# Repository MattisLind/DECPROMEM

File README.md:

# DECPROMEM

Project finished (almost) and deemed working as intended.

My 1 meg machine now shows 1536 kWord, i.e. 3 Mega byte of memory. The Gerbers in the kicad directory is updated. The final JED file to program the AYTF1508 is in the VHDL directory. Programming the board requires the rather expensive ATDH1150USB JTAG device. But supposedely other devices can be used. Check more here on [this page](https://github.com/peterzieba/5Vpld)

The board can be populated with either 1 or 2 chips. One chip will take your machine from 1 meg to the maximum of three meg. If you have less than 1 meg in your base machine a two chip card is better. The SIZE jumper need to be inserted if you only have one chip. 

The board can be populated with either AMD DP8307 bus tranceivers (which are obsolete but can be found online) or 74ALS640 which should be compatible. However not 100 % pincompatible, thus the overlapping layout.

I have not tested the board with one single chip or using 74ALS640 tranceivers (but it has been tested in simulation).

Debugging of the card took some time. Problems found during debugging:

1. The height of the card was 100 mil to high. Had to carefully cut off the card a bit to get it into the card cage. Lessons learned: Always double (triple) check dimensions. The new layout has this fixed.
2. The brand new 20 MHz crystal from Mouser didn't oscillate. While investigating this I found that certain signals of the Microchip 25LC08A SPI EEPROM require a 50 ns setup time. With a 20 MHz that would be on the margin unless the state machine was modified. I used a 14.7456 MHz crystal oscillator that I happened to find in my drawer.
3. SDENL need to be gated with with signals that indicate that the card is selected. Either IO read or memory read. Otherwise it will clash with other drivers on the bus.
4. The schematic had mixed up the MCELOW, NMCEHIGH and MLE signals. The good thibng it was easy to reroute those signals in the CPLD.
5. The BRPLYL signal was not developed internally. The OC signal was created by setting the signal to either 0 or Z. Somehow Yosys optimzed this away unless I set an attribute on those signal.
6. The BIOSEL signal has to be latched as an address signal. But since the SSxL signal is basically created with the latched BIOSEL on the motherboard there is no point in using BIOSEL anyway. Removed it from the CPLD VHLD logic.
7. The test bench for the SPI ROM wasn't perfect. It mismatched a bit from how reality worked so the SPI communication didn't work properly. The counter has to be incremented on falling edge instead of rising edge. Lessons learned is that good testbed is crucial. Still need to fix that SPIROM test device which still do the wrong thing.
8. When testing it read random number of bytes from the SPI ROM. Sometimes 30 sometimes 50. A metastability issues caused the HOLDL signal to get stuck. Syncing the readPort0 signal on the rising edge solved the problem.
9. The memoryAccess signal generated was spuriously active. Lilkely to be an effect of the fact that it is developed by a long chain of logic which ripples through. By syncing the memoryAccess signal with the clock and gating the clock to with the ASL signal solved the problem. Also making sure that all variables used in the process is the same length.

The development board with a lot of test points.

The original board:

This project aims at creating a modern memory board for the 1985 vintage DEC Professional series of computers with CTI bus. The idea is to use SRAM technology and programmable logic to implement all the random logic needed. The diagnostic ROM that all CTI bus boards need to have is implemented in a SPI EEPROM chip. The programmable logic choosen for this project is the Atmel / Microchip ATF1508 since it is the only contemporary chip that is 5V. I will be using one or two 1Mx16 SRAM chip which also are 5V. A small SPI EEPROM will contain the diag software. There will not be any parity on board whihc means that the diag software need to be changed compared to the original so that it doesn't test the parity generating and checking circuits on board.

The idea with this project is also to learn a bit about the CTI bus so that I can take on the DECNA-replica project later on which aims at creating a modern replacement for the DECNA board whihc is nearly impossible to find. This will also be using a ATF1508 CPLD.

## Firmware

The original diagnostic firmware is stored in either a 2716 or 2732 (jumper selectable on the board according to the manual), but only the lower 1k byte is actually used. 

I have been using xhomer project which I modified to create an execution trace. Thereby I could figure out how the Professional is dealing with CTI bus boards.
All boards has a board ID which identify the board. This is a two byte octal number which is also printed on the board handle. The memory board is 34 for example. Most likely the board id has significance to how the board is handled but I have obnly researched the memory board this far.

All CTI bus boards have a writeable register located at base address + 2 which resets the pointer to the ID / diagnostic ROM when written to it. Then reads from the base address will return byte by byte from the ID / diag ROM. The process is the following:

1. Read the two ID bytes. Decide how to handle board.
2. Reset pointer and read the first 12 bytes into memory. Byte 2 is compared with 0377. I am not sure what happens if it is not matching. Then it uses byte 6 to indicate the number of 128 word blocks that are present in the memory.
3. It resets the pointer again and start reading the number indicated byte location 6 above of 128 word blocks and calculates a checksum. More on the checksum algorithm later.
4. It then resets the pointer again and just read and skip the first 12 bytes. Then it reads in the following 14 bytes.
5. Location 23 and 24 is the size of the actual program code following, where byte 23 is the low byte and 24 is the high byte. The resuling 16 bit integer is then used when reading in the program code.
6. While reading the program code the same type of checksum is calculated again over this smaller block.

### Checksum algorithm

The checksum algorithm is a combination of xor and shift operations.
1. A checksum accumulator is initiated to 0177777
2. Two bytes are read in to form a word.
3. The data is xor:ed with the accumulator contents.
4. The accumulator is shifted on step to the left.
5. The bit overflowing 16 bits is creating a carry bit which either one or zero.
6. The carry bit is added to the accumulator.
7. The process repeats at 2 until all words has been read.
8. If the result in the accumulator is zero when all words has vbeen read then we have a good checksum.

### Firmware functions

The firmware is used to initialize and test the board. The process is the following:
1. Calculates the size of the board. There are two jumpers on the board which give the actual size of the board. I think actually this calculation is buggy for boards with 256 k chips!
2. It compares the calculated size with the value used as base value for this memory array. If the base address indicate that we already configured 3 Megabytes of memory we bail out with an error code.
3. Enable the memory board with the base value given from the system.
4. If memory size of the board give that it will exceed the 3 meg limit it tests so that there is no response from the memory for addresses aboev 3 meg.
5. It now enables the functionaity where  the memory board by design writes the oposite parity value which means that a read will cause a trap, thereby checking so that the parity circuits work.
6. Sets back to normal partity handling and checks the entire array.
7. If everything is ok it reports back the new base value which is essentially the old base value plus the size of this memory array. If something wrong has been detected then it will turn off the memory board and issue a fault code as return value.

### Firmware building

Since I want to change the firmware to not have any parity checking I need to build it using the macro-11 assembler and then compute the two levels of checksums to get a working rom-image to use on the board or in Xhomer. The macro-11 program creates an object file which has to be converted into a raw binary file. This is done using the obj2bin tool.

The Makefile provided should do all the work of doing all this provided that the correct paths to the macro-11 and obj2bin binaries has been given.

### Reminaing to be done.

1. Test with 74ALS640 chips.
2. Test with a single memory chip rather than two.
3. Test on machine with less than 1 meg or more than 1 meg.
4. What happens if there is another memory board in the machine? Should work but not tested yet.

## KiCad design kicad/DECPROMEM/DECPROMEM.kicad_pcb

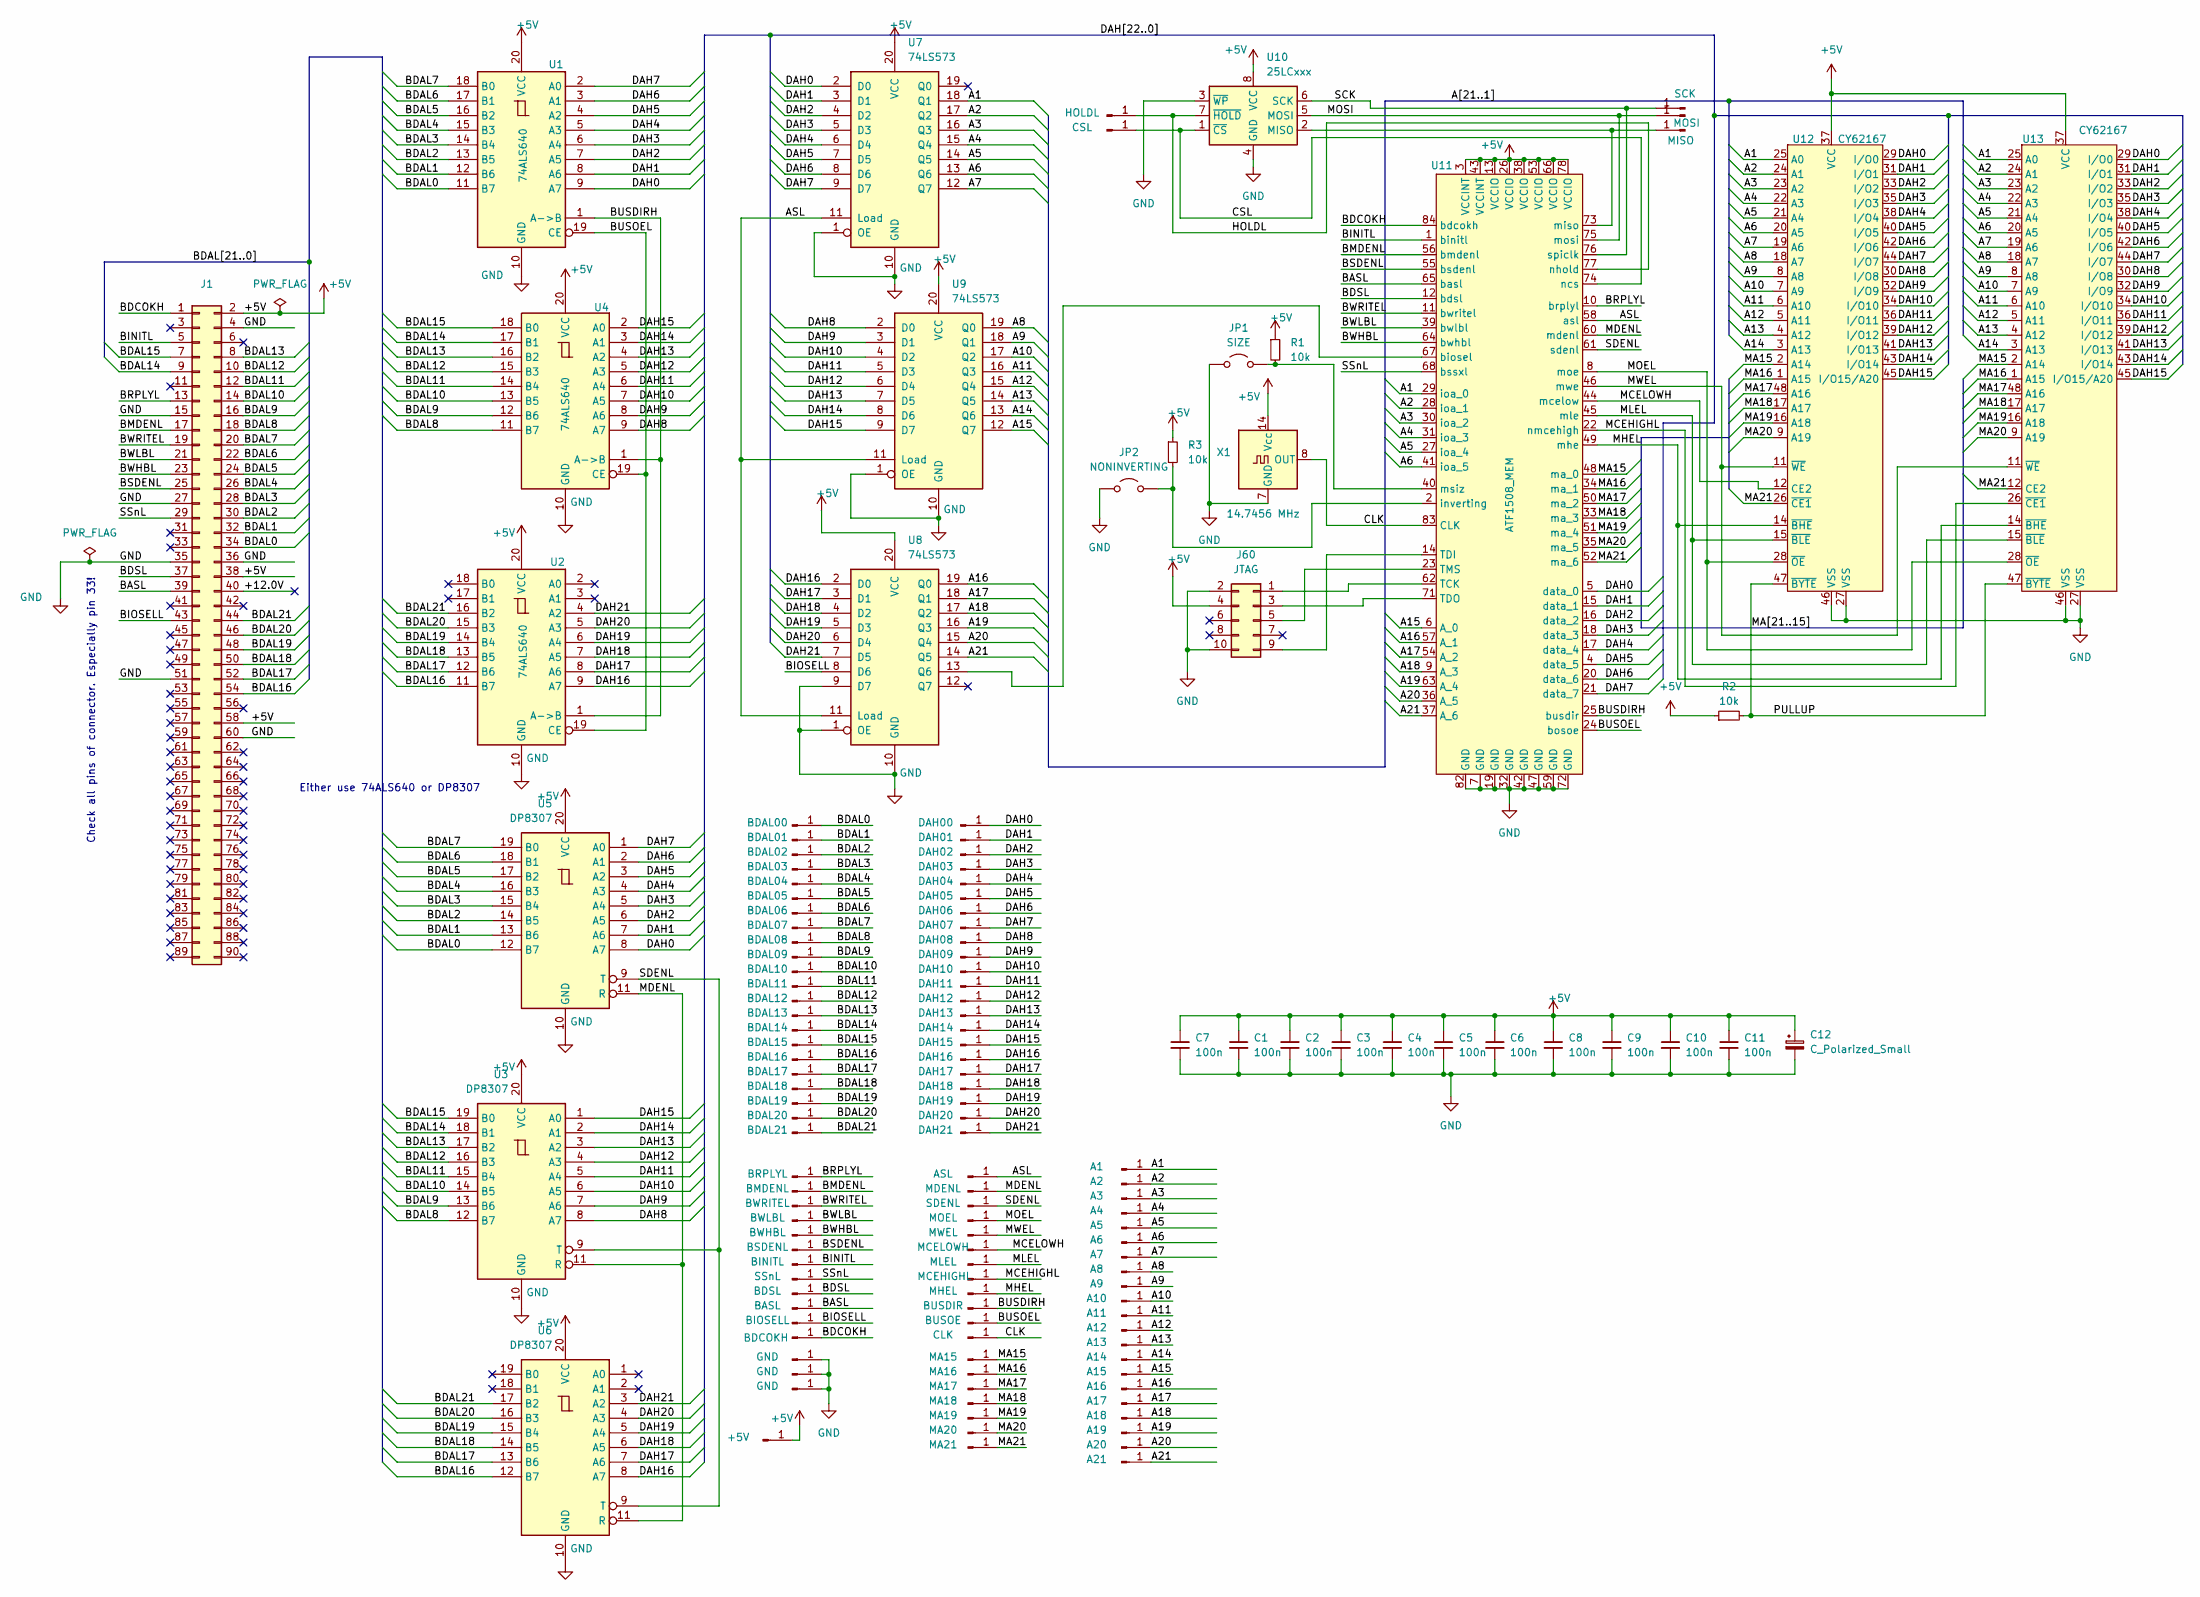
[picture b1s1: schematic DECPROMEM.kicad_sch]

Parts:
C1, C2, C3, C4, C5, C6, C7, C8, C9, C10, C11: 100n; C_Disc_D4.3mm_W1.9mm_P5.00mm
C12: C_Polarized_Small; CP_Radial_Tantal_D4.5mm_P5.00mm
J1: CTI-90
J2: BDAL00; Testpoint
J3: BDAL01; Testpoint
J4: BDAL02; Testpoint
J5: BDAL03; Testpoint
J6: BDAL04; Testpoint
J7: BDAL05; Testpoint
J8: BDAL06; Testpoint
J9: BDAL07; Testpoint
J10: BDAL08; Testpoint
J11: BDAL09; Testpoint
J12: BDAL10; Testpoint
J13: BDAL11; Testpoint
J14: BDAL12; Testpoint
J15: BDAL13; Testpoint
J16: BDAL14; Testpoint
J17: BDAL15; Testpoint
J18: BDAL16; Testpoint
J19: BDAL17; Testpoint
J20: BDAL18; Testpoint
J21: BDAL19; Testpoint
J22: BDAL20; Testpoint
J23: BDAL21; Testpoint
J24: BRPLYL; Testpoint
J25: BMDENL; Testpoint
J26: BWRITEL; Testpoint
J27: BWLBL; Testpoint
J28: BWHBL; Testpoint
J29: BSDENL; Testpoint
J30: SSnL; Testpoint
J31: BDSL; Testpoint
J32: BASL; Testpoint
J33: BIOSELL; Testpoint
J34: BDCOKH; Testpoint
J35, J36, J37: GND; Testpoint
J38: DAH00; Testpoint
J39: DAH01; Testpoint
J40: DAH02; Testpoint
J41: DAH03; Testpoint
J42: DAH04; Testpoint
J43: DAH05; Testpoint
J44: DAH06; Testpoint
J45: DAH07; Testpoint
J46: DAH08; Testpoint
J47: DAH09; Testpoint
J48: DAH10; Testpoint
J49: DAH11; Testpoint
J50: DAH12; Testpoint
J51: DAH13; Testpoint
J52: DAH14; Testpoint
J53: DAH15; Testpoint
J54: DAH16; Testpoint
J55: DAH17; Testpoint
J56: DAH18; Testpoint
J57: DAH19; Testpoint
J58: DAH20; Testpoint
J59: DAH21; Testpoint
J60: JTAG; PinHeader_2x05_P2.54mm_Vertical
J61: ASL; Testpoint
J62: MDENL; Testpoint
J63: SDENL; Testpoint
J64: MOEL; Testpoint
J65: MWEL; Testpoint
J66: MCELOWH; Testpoint
J67: MLEL; Testpoint
J68: MCEHIGHL; Testpoint
J69: MHEL; Testpoint
J70: BUSDIR; Testpoint
J71: BUSOE; Testpoint
J72: CLK; Testpoint
J73: MA15; Testpoint
J74: MA16; Testpoint
J75: MA17; Testpoint
J76: MA18; Testpoint
J77: MA19; Testpoint
J78: MA20; Testpoint
J79: MA21; Testpoint
J80: HOLDL; Testpoint
J81: CSL; Testpoint
J82: SCK; Testpoint
J83: MOSI; Testpoint
J84: MISO; Testpoint
J85: BINITL; Testpoint
J86: A1; Testpoint
J87: A2; Testpoint
J88: A3; Testpoint
J89: A4; Testpoint
J90: A5; Testpoint
J91: A6; Testpoint
J92: A7; Testpoint
J93: A8; Testpoint
J94: A9; Testpoint
J95: A10; Testpoint
J96: A11; Testpoint
J97: A12; Testpoint
J98: A13; Testpoint
J99: A14; Testpoint
J100: A15; Testpoint
J101: A16; Testpoint
J102: A17; Testpoint
J103: A18; Testpoint
J104: A19; Testpoint
J105: A20; Testpoint
J106: A21; Testpoint
J107: +5V; Testpoint
JP1: SIZE; PinHeader_1x02_P2.54mm_Vertical
JP2: NONINVERTING; PinHeader_1x02_P2.54mm_Vertical
R1, R2, R3: 10k; R_Axial_DIN0207_L6.3mm_D2.5mm_P10.16mm_Horizontal
U1, U2, U4: 74ALS640; DIP-20_W7.62mm_Socket
U3, U5, U6: DP8307; DIP-20_W7.62mm_Socket
U7, U8, U9: 74LS573; DIP-20_W7.62mm_Socket
U10: 25LCxxx; DIP-8_W7.62mm
U11: ATF1508_MEM; PLCC-84_THT-Socket
U12, U13: CY62167; TSOP-I-48_18.4x12mm_P0.5mm
X1: 14.7456 MHz; Oscillator_DIP-14

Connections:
+5V: C1.1, C2.1, C3.1, C4.1, C5.1, C6.1, C7.1, C8.1, C9.1, C10.1, C11.1, C12.1, J1.2, J1.38, J1.58, J60.4, J107.1, R1.1, R2.1, R3.1, U1.20 (VCC), U2.20 (VCC), U3.20 (VCC), U4.20 (VCC), U5.20 (VCC), U6.20 (VCC), U7.20 (VCC), U8.20 (VCC), U9.20 (VCC), U10.8 (VCC), U11.3 (VCCINT), U11.13 (VCCIO), U11.26 (VCCIO), U11.38 (VCCIO), U11.43 (VCCINT), U11.53 (VCCIO), U11.66 (VCCIO), U11.78 (VCCIO), U12.37 (VCC), U13.37 (VCC), X1.14 (Vcc)
/+12.0V: J1.40
/A1: J86.1, U7.18 (Q1), U11.29 (ioa_0), U12.25 (A0), U13.25 (A0)
/A2: J87.1, U7.17 (Q2), U11.28 (ioa_1), U12.24 (A1), U13.24 (A1)
/A3: J88.1, U7.16 (Q3), U11.30 (ioa_2), U12.23 (A2), U13.23 (A2)
/A4: J89.1, U7.15 (Q4), U11.31 (ioa_3), U12.22 (A3), U13.22 (A3)
/A5: J90.1, U7.14 (Q5), U11.27 (ioa_4), U12.21 (A4), U13.21 (A4)
/A6: J91.1, U7.13 (Q6), U11.41 (ioa_5), U12.20 (A5), U13.20 (A5)
/A7: J92.1, U7.12 (Q7), U12.19 (A6), U13.19 (A6)
/A8: J93.1, U9.19 (Q0), U12.18 (A7), U13.18 (A7)
/A9: J94.1, U9.18 (Q1), U12.8 (A8), U13.8 (A8)
/A10: J95.1, U9.17 (Q2), U12.7 (A9), U13.7 (A9)
/A11: J96.1, U9.16 (Q3), U12.6 (A10), U13.6 (A10)
/A12: J97.1, U9.15 (Q4), U12.5 (A11), U13.5 (A11)
/A13: J98.1, U9.14 (Q5), U12.4 (A12), U13.4 (A12)
/A14: J99.1, U9.13 (Q6), U12.3 (A13), U13.3 (A13)
/A15: J100.1, U9.12 (Q7), U11.6 (A_0)
/A16: J101.1, U8.19 (Q0), U11.57 (A_1)
/A17: J102.1, U8.18 (Q1), U11.54 (A_2)
/A18: J103.1, U8.17 (Q2), U11.9 (A_3)
/A19: J104.1, U8.16 (Q3), U11.63 (A_4)
/A20: J105.1, U8.15 (Q4), U11.36 (A_5)
/A21: J106.1, U8.14 (Q5), U11.37 (A_6)
/ASL: J61.1, U7.11 (Load), U8.11 (Load), U9.11 (Load), U11.58 (asl)
/BASL: J1.39, J32.1, U11.65 (basl)
/BDAL0: J1.34, J2.1, U1.11 (B7), U5.12 (B7)
/BDAL1: J1.32, J3.1, U1.12 (B6), U5.13 (B6)
/BDAL2: J1.30, J4.1, U1.13 (B5), U5.14 (B5)
/BDAL3: J1.28, J5.1, U1.14 (B4), U5.15 (B4)
/BDAL4: J1.26, J6.1, U1.15 (B3), U5.16 (B3)
/BDAL5: J1.24, J7.1, U1.16 (B2), U5.17 (B2)
/BDAL6: J1.22, J8.1, U1.17 (B1), U5.18 (B1)
/BDAL7: J1.20, J9.1, U1.18 (B0), U5.19 (B0)
/BDAL8: J1.18, J10.1, U3.12 (B7), U4.11 (B7)
/BDAL9: J1.16, J11.1, U3.13 (B6), U4.12 (B6)
/BDAL10: J1.14, J12.1, U3.14 (B5), U4.13 (B5)
/BDAL11: J1.12, J13.1, U3.15 (B4), U4.14 (B4)
/BDAL12: J1.10, J14.1, U3.16 (B3), U4.15 (B3)
/BDAL13: J1.8, J15.1, U3.17 (B2), U4.16 (B2)
/BDAL14: J1.9, J16.1, U3.18 (B1), U4.17 (B1)
/BDAL15: J1.7, J17.1, U3.19 (B0), U4.18 (B0)
/BDAL16: J1.54, J18.1, U2.11 (B7), U6.12 (B7)
/BDAL17: J1.52, J19.1, U2.12 (B6), U6.13 (B6)
/BDAL18: J1.50, J20.1, U2.13 (B5), U6.14 (B5)
/BDAL19: J1.48, J21.1, U2.14 (B4), U6.15 (B4)
/BDAL20: J1.46, J22.1, U2.15 (B3), U6.16 (B3)
/BDAL21: J1.44, J23.1, U2.16 (B2), U6.17 (B2)
/BDCOKH: J1.1, J34.1, U11.84 (bdcokh)
/BDSL: J1.37, J31.1, U11.12 (bdsl)
/BINITL: J1.5, J85.1, U11.1 (binitl)
/BIOSELL: J1.43, J33.1, U8.8 (D6)
/BMDENL: J1.17, J25.1, U11.56 (bmdenl)
/BRPLYL: J1.13, J24.1, U11.10 (brplyl)
/BSDENL: J1.25, J29.1, U11.55 (bsdenl)
/BUSDIRH: J70.1, U1.1 (A->B), U2.1 (A->B), U4.1 (A->B), U11.25 (busdir)
/BUSOEL: J71.1, U1.19 (CE), U2.19 (CE), U4.19 (CE), U11.24 (bosoe)
/BWHBL: J1.23, J28.1, U11.64 (bwhbl)
/BWLBL: J1.21, J27.1, U11.39 (bwlbl)
/BWRITEL: J1.19, J26.1, U11.11 (bwritel)
/CLK: J72.1, U11.83 (CLK), X1.8 (OUT)
/CSL: J81.1, U10.1 (~CS), U11.74 (ncs)
/DAH0: J38.1, U1.9 (A7), U5.8 (A7), U7.2 (D0), U11.5 (data_0), U12.29 (I/O0), U13.29 (I/O0)
/DAH1: J39.1, U1.8 (A6), U5.7 (A6), U7.3 (D1), U11.15 (data_1), U12.31 (I/O1), U13.31 (I/O1)
/DAH2: J40.1, U1.7 (A5), U5.6 (A5), U7.4 (D2), U11.16 (data_2), U12.33 (I/O2), U13.33 (I/O2)
/DAH3: J41.1, U1.6 (A4), U5.5 (A4), U7.5 (D3), U11.18 (data_3), U12.35 (I/O3), U13.35 (I/O3)
/DAH4: J42.1, U1.5 (A3), U5.4 (A3), U7.6 (D4), U11.17 (data_4), U12.38 (I/O4), U13.38 (I/O4)
/DAH5: J43.1, U1.4 (A2), U5.3 (A2), U7.7 (D5), U11.4 (data_5), U12.40 (I/O5), U13.40 (I/O5)
/DAH6: J44.1, U1.3 (A1), U5.2 (A1), U7.8 (D6), U11.20 (data_6), U12.42 (I/O6), U13.42 (I/O6)
/DAH7: J45.1, U1.2 (A0), U5.1 (A0), U7.9 (D7), U11.21 (data_7), U12.44 (I/O7), U13.44 (I/O7)
/DAH8: J46.1, U3.8 (A7), U4.9 (A7), U9.2 (D0), U12.30 (I/O8), U13.30 (I/O8)
/DAH9: J47.1, U3.7 (A6), U4.8 (A6), U9.3 (D1), U12.32 (I/O9), U13.32 (I/O9)
/DAH10: J48.1, U3.6 (A5), U4.7 (A5), U9.4 (D2), U12.34 (I/O10), U13.34 (I/O10)
/DAH11: J49.1, U3.5 (A4), U4.6 (A4), U9.5 (D3), U12.36 (I/O11), U13.36 (I/O11)
/DAH12: J50.1, U3.4 (A3), U4.5 (A3), U9.6 (D4), U12.39 (I/O12), U13.39 (I/O12)
/DAH13: J51.1, U3.3 (A2), U4.4 (A2), U9.7 (D5), U12.41 (I/O13), U13.41 (I/O13)
/DAH14: J52.1, U3.2 (A1), U4.3 (A1), U9.8 (D6), U12.43 (I/O14), U13.43 (I/O14)
/DAH15: J53.1, U3.1 (A0), U4.2 (A0), U9.9 (D7), U12.45 (I/O15/A20), U13.45 (I/O15/A20)
/DAH16: J54.1, U2.9 (A7), U6.8 (A7), U8.2 (D0)
/DAH17: J55.1, U2.8 (A6), U6.7 (A6), U8.3 (D1)
/DAH18: J56.1, U2.7 (A5), U6.6 (A5), U8.4 (D2)
/DAH19: J57.1, U2.6 (A4), U6.5 (A4), U8.5 (D3)
/DAH20: J58.1, U2.5 (A3), U6.4 (A3), U8.6 (D4)
/DAH21: J59.1, U2.4 (A2), U6.3 (A2), U8.7 (D5)
/HOLDL: J80.1, U10.7 (~HOLD), U11.77 (nhold)
/MA15: J73.1, U11.48 (ma_0), U12.2 (A14), U13.2 (A14)
/MA16: J74.1, U11.34 (ma_1), U12.1 (A15), U13.1 (A15)
/MA17: J75.1, U11.50 (ma_2), U12.48 (A16), U13.48 (A16)
/MA18: J76.1, U11.33 (ma_3), U12.17 (A17), U13.17 (A17)
/MA19: J77.1, U11.51 (ma_4), U12.16 (A18), U13.16 (A18)
/MA20: J78.1, U11.35 (ma_5), U12.9 (A19), U13.9 (A19)
/MA21: J79.1, U11.52 (ma_6), U12.26 (~CE1), U13.12 (CE2)
/MCEHIGHL: J68.1, U11.22 (nmcehigh), U13.26 (~CE1)
/MCELOWH: J66.1, U11.44 (mcelow), U12.12 (CE2)
/MDENL: J62.1, U3.11 (R), U5.11 (R), U6.11 (R), U11.60 (mdenl)
/MHEL: J69.1, U11.49 (mhe), U12.14 (~BHE), U13.14 (~BHE)
/MLEL: J67.1, U11.45 (mle), U12.15 (~BLE), U13.15 (~BLE)
/MOEL: J64.1, U11.8 (moe), U12.28 (~OE), U13.28 (~OE)
/MOSI: J83.1, U10.5 (MOSI), U11.75 (mosi)
/MWEL: J65.1, U11.46 (mwe), U12.11 (~WE), U13.11 (~WE)
/PULLUP: R2.2, U12.47 (~BYTE), U13.47 (~BYTE)
/SCK: J82.1, U10.6 (SCK), U11.76 (spiclk)
/SDENL: J63.1, U3.9 (T), U5.9 (T), U6.9 (T), U11.61 (sdenl)
/SSnL: J1.29, J30.1, U11.68 (bssxl)
GND: C1.2, C2.2, C3.2, C4.2, C5.2, C6.2, C7.2, C8.2, C9.2, C10.2, C11.2, C12.2, J1.4, J1.15, J1.27, J1.35, J1.36, J1.51, J1.60, J35.1, J36.1, J37.1, J60.2, J60.10, JP1.1 (A), JP2.1 (A), U1.10 (GND), U2.10 (GND), U3.10 (GND), U4.10 (GND), U5.10 (GND), U6.10 (GND), U7.1 (OE), U7.10 (GND), U8.1 (OE), U8.9 (D7), U8.10 (GND), U9.1 (OE), U9.10 (GND), U10.3 (~WP), U10.4 (GND), U11.7 (GND), U11.19 (GND), U11.32 (GND), U11.42 (GND), U11.47 (GND), U11.59 (GND), U11.72 (GND), U11.82 (GND), U12.27 (VSS), U12.46 (VSS), U13.27 (VSS), U13.46 (VSS), X1.7 (GND)
unnamed: J60.1, U11.62 (TCK)
unnamed: J60.3, U11.71 (TDO)
unnamed: J60.5, U11.23 (TMS)
unnamed: J60.9, U11.14 (TDI)
unnamed: J84.1, U10.2 (MISO), U11.73 (miso)
unnamed: JP1.2 (B), R1.2, U11.40 (msiz)
unnamed: JP2.2 (B), R3.2, U11.2 (inverting)
unnamed: U8.13 (Q6), U11.67 (biosel)

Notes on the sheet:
Either use 74ALS640 or DP8307
Check all pins of connector. Especially pin 33!

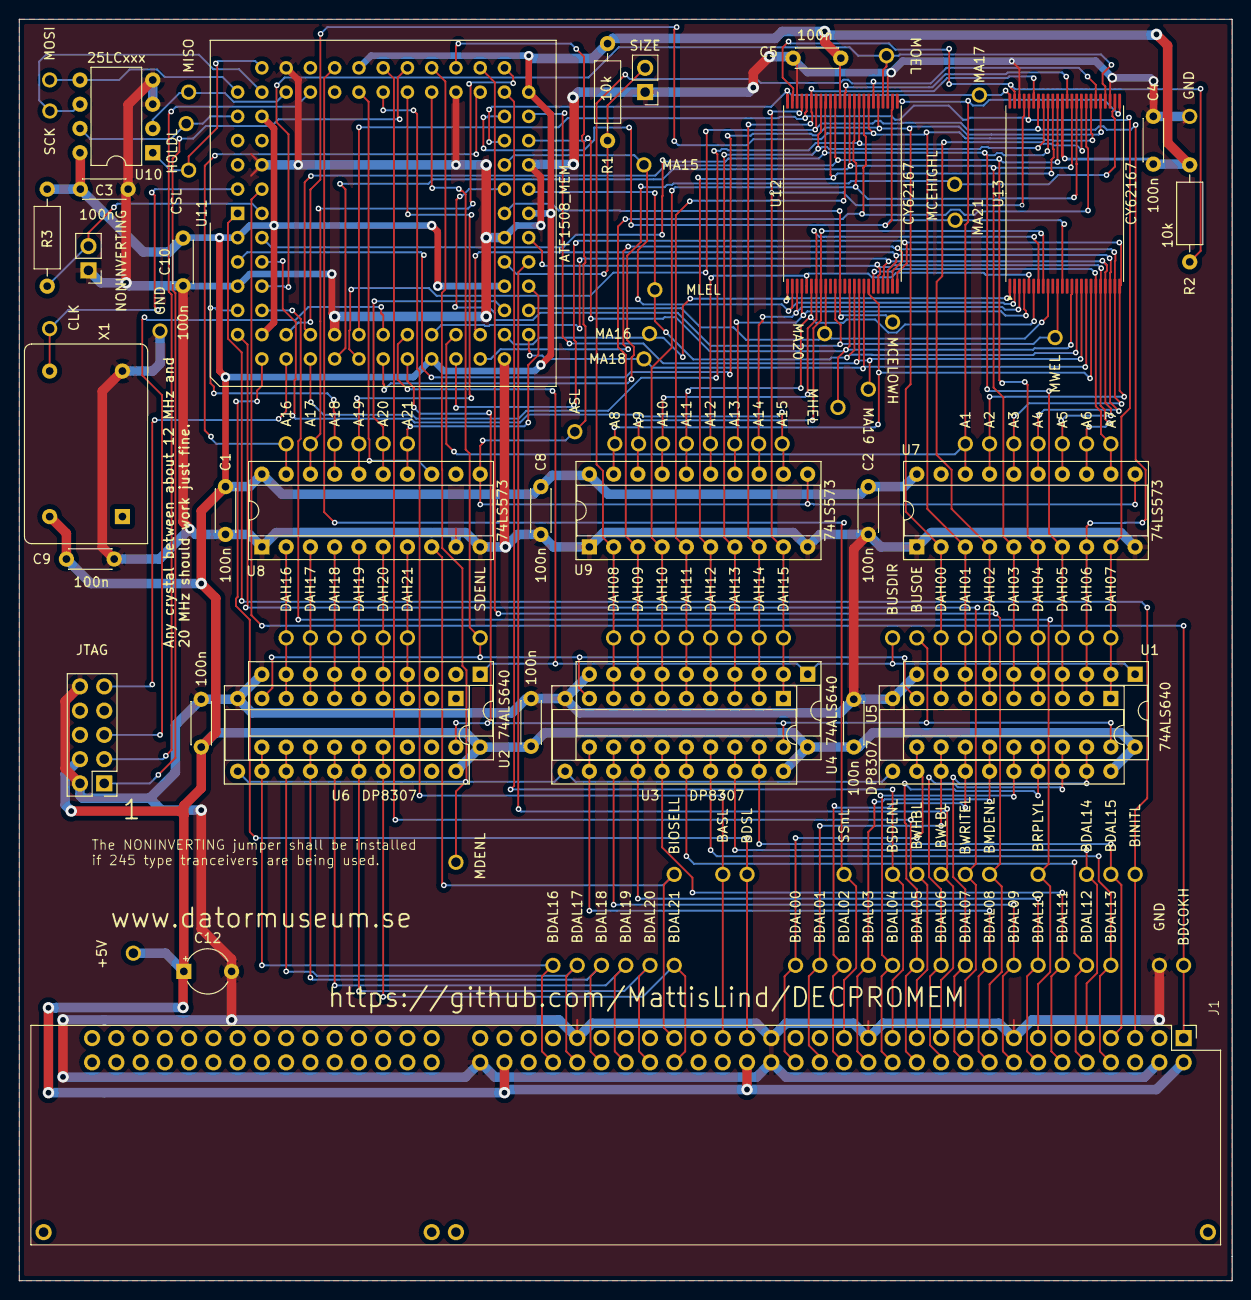
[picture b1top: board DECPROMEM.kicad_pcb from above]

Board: 2 copper layers, 127.0 x 132.1 mm, 138 parts (0 on the bottom side), 111 nets.

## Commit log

2024-03-23 Picture memory board
2024-03-23 Original ROM code
2024-03-23 Added the assembly file
2024-03-23 Fixed name of picture.
2024-03-23 Added a Makefile and code to calculate the checksums.
2024-03-23 Fixed a build system for rom images.
2024-03-23 Patched so that we now support 2 or 4 meg board without parity check.
2024-03-26 This version has been tested with patched xhomer and provide a total of 3meg regardless of 256k or 1 meg of base memory.
2024-03-28 Made the CSR select number of 32k chunks to add.
2024-03-31 Included macro11 and obj2bin as submodules and fixed the Makefile to build it all.
2024-03-31 Adding a embryo for the VHDL code.
2024-04-04 Trying to simulate the eeprom as a testbench.
2024-04-04 Making a utility to convert the binary rom file to vhdl.
2024-04-06 Fixed ROM builder.
2024-04-06 decpromem.vhdl
2024-04-06 Fixed ROM generator to support one bit ROM output.
2024-04-07 Fixed hold and removed use of intermediary register.
2024-04-07 Removed commented out code.
2024-04-08 Trying to run the fitter.
2024-04-10 Fixed VHDL. Now it is possible to fit it into a ATF1508.
2024-04-10 Making the testbench more complete.
2024-04-20 Added function to test read access and added brplyl functionality.
2024-04-20 Fixed reset of counter.
2024-04-20 Added a memory chip so we can test the full solution.
2024-04-21 Complete restructuring of test.
2024-04-22 Refactor to simulate actual chips used with correct pin-numbering to rule out all mistakes.
2024-04-22 Fixed error in SPIROM and added a wait state indicator.
2024-04-23 Testing memory a bit and IO registers.
2024-04-24 Fixed full test bench for memory. Testing all sorts of legal and illegal accesses.
2024-04-25 Added 74ALS640.
2024-04-25 Tested both 74ALS640 and DP8307 tranceivers. Both works.
2024-04-29 Fixed the pins so that a layout would be possible.
2024-04-30 Add bdcokh signal and corrected the pin assignments.
2024-05-26 Have basl buffered in CPLD.
2024-05-26 Adding Kicad schema .
2024-05-26 Updated schematic.
2024-06-02 Updates to schematic.
2024-06-02 Starting to do the layout.
2024-06-02 More layout done.
2024-06-02 Had to add more test points.
2024-07-09 Fixed missing directive
2025-01-30 Added pdf file and all the gerbers
2025-07-29 Fixed the size jumper.
2025-07-30 Added jedec file.
2025-07-30 Added ATF1508 jedec instead.
2025-07-30 Added PIN declarations to force fitter to use these pins.
2025-07-30 Updating JED file.
2025-07-30 Updated macro11 and yosys docker build system.
2025-07-30 Updated JED file after fixing pinfile logic in the workflow.
2025-07-30 Adding built rom file for convenience.
2025-08-01 Fixed so that tranceivers are only enabled when accessing the port or memory when reading data otherwise it would clash with other devices.
2025-08-02 Removed use of biosel since the latched version of biosel is used for developing ssnxl signal which we are using.
2025-08-03 The layout had mixed up nmcehigh, mcelow and mle. Fixed in CPLD pin assignment.
2025-08-03 Needed to set keep attribute to make sure yosys is not optimizing away the OE signal.
2025-08-03 Trying to debug bu assigning signals to ma pins.
2025-08-03 Modified equations a bit.
2025-08-03 Trying to understand why breply is active when it shouldn't.
2025-08-04 The INITIAL state transition was moved by mistake to rising edge while it should have been kept at falling edge.
2025-08-04 Only clocking in 7 bits before going into hold. Need 8 bits.
2025-08-04 Revert "Only clocking in 7 bits before going into hold. Need 8 bits."
    This reverts commit 62e5ad3ef8668f1cab0c78664bc3677645271ade.
2025-08-04 Counter incremented on falling edge instead of rising edge.
2025-08-04 Potential metastability issue with readPort0 signal is statemachine.
2025-08-05 More debugging. Now outputing memoryAccess signal as ma(6) and also the memory address bits in ma(5) .. ma(0).
2025-08-05 Testing with hard coded base value.
2025-08-06 New try at fixing the memory mapping.
2025-08-06 Trying another variant.
2025-08-06 Make logic simpler to test.
2025-08-06 Adding a memoryAccess2 pin to be able to compare side by side.
2025-08-06 Made all variables of equal size.
2025-08-07 Playing around to understand what is going wrong.
2025-08-07 Yet more testing
2025-08-07 Adding back vTop calculation instead of hardcoded value. Last commit was working. Now this is interesting...
2025-08-07 Adding back high memory address bits calculation as well. Last commit worked just fine.
2025-08-07 Clean up and removing test code and commented out code. Last commit was also working like a charm.
2025-08-07 Updated the schematics and layout to fix a bunch small errors.
2025-08-07 Update mem.asm
    Missing directive here as well.
2025-08-10 Updating pinout for large connector since it was wrong. Added support for 245 trancerivers.
2025-08-10 Fixed ATF1508 symbol to have the right pinout.
2025-08-14 Fixing A - B port mixup on trsnceivers.
2025-08-14 Fixing texts in schematic
2025-08-14 Updated zip-file.
